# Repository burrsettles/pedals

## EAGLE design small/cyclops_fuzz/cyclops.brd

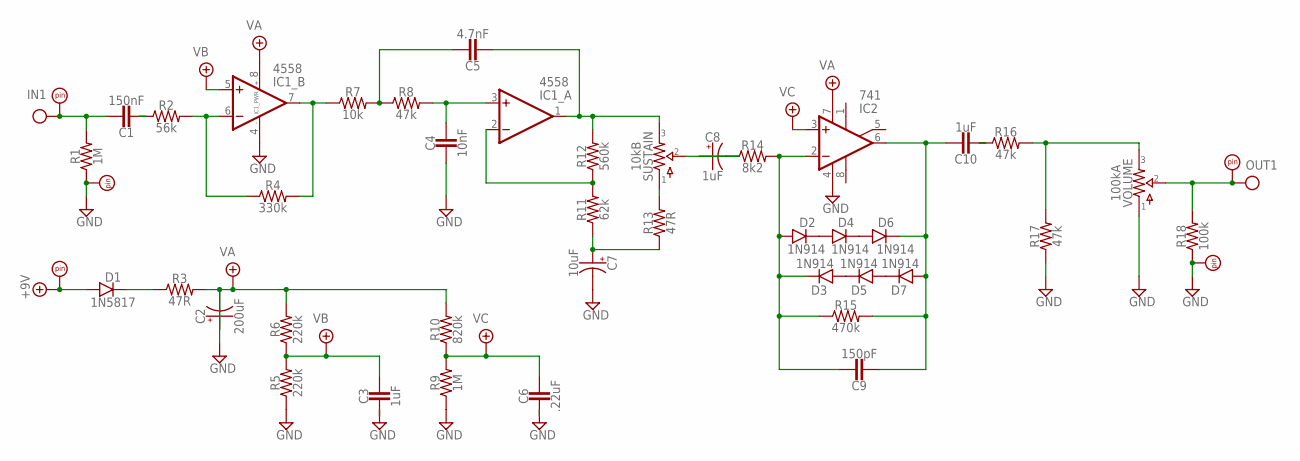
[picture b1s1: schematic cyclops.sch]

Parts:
C1: 150nF; BOX_SMALL
C2: 200uF; 063_025
C3, C10: 1uF; BOX_MED
C4: 10nF; BOX_SMALL
C5: 4.7nF; BOX_SMALL
C6: .22uF; BOX_SMALL
C7: 10uF; 050_020_1
C8: 1uF; 050_020_1
C9: 150pF; BOX_SMALL
D1: 1N5817; DO41-2
D2, D3, D4, D5, D6, D7: 1N914; DO35-2
IC1: 4558; DIL08
IC2: 741; DIL08
PAD1, PAD2, PAD5: PADSQR; SQUARE
PAD3, PAD4: PADRND; ROUND
R1, R9: 1M; R0207/2V
R2: 56k; R0207/2V
R3, R13: 47R; R0207/2V
R4: 330k; R0207/2V
R5, R6: 220k; R0207/2V
R7: 10k; R0207/2V
R8, R16, R17: 47k; R0207/2V
R10: 820k; R0207/2V
R11: 62k; R0207/2V
R12: 560k; R0207/2V
R14: 8k2; R0207/2V
R15: 470k; R0207/2V
R18: 100k; R0207/2V
SUSTAIN: 10kB; 2262_TRIM
VOLUME: 100kA; PADS_SMALL

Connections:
+9V: D1.A, PAD1.1
GND: C2.-, C3.2, C4.2, C6.2, C7.-, IC1.4 (V-), IC2.4 (V-), PAD3.1, PAD4.1, R1.1, R5.1, R9.1, R17.1, R18.1, VOLUME.1
IN: C1.1, PAD2.1, R1.2
unnamed: C1.2, R2.1
unnamed: C10.2, R16.1
unnamed: R16.2, R17.2, VOLUME.3
unnamed: IC1.6 (-IN), R2.2, R4.1
unnamed: IC1.7 (OUT), R4.2, R7.1
unnamed: C5.1, R7.2, R8.1
unnamed: C4.1, IC1.3 (+IN), R8.2
unnamed: C5.2, IC1.1 (OUT), R12.2, SUSTAIN.3
unnamed: IC1.2 (-IN), R11.2, R12.1
unnamed: C7.+, R11.1, R13.1
unnamed: R13.2, SUSTAIN.1
unnamed: D1.C, R3.1
unnamed: C8.-, SUSTAIN.2
unnamed: C8.+, R14.1
unnamed: C9.1, D2.A, D3.C, IC2.2 (-IN), R14.2, R15.1
unnamed: D2.C, D4.A
unnamed: D4.C, D6.A
unnamed: D5.A, D7.C
unnamed: D3.A, D5.C
unnamed: C9.2, C10.1, D6.C, D7.A, IC2.6 (OUT), R15.2
OUT: PAD5.1, R18.2, VOLUME.2
VA: C2.+, IC1.8 (V+), IC2.7 (V+), R3.2, R6.2, R10.2
VB: C3.1, IC1.5 (+IN), R5.2, R6.1
VC: C6.1, IC2.3 (+IN), R9.2, R10.1

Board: 2 copper layers, 44 parts (0 on the bottom side), 27 nets, no tracks yet.

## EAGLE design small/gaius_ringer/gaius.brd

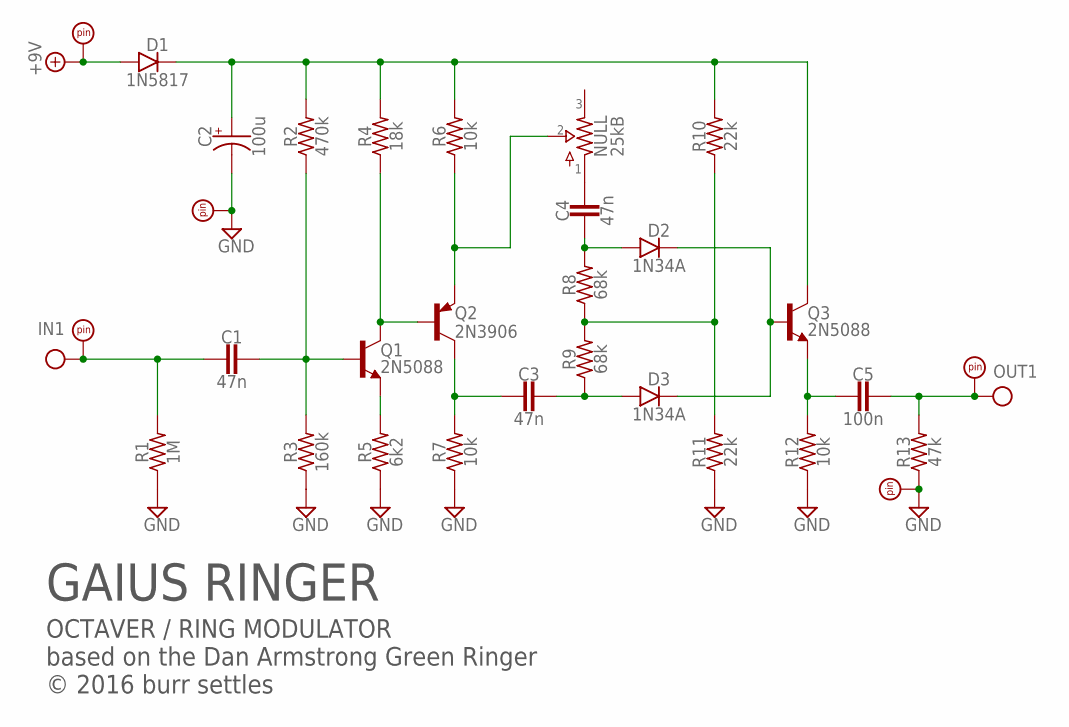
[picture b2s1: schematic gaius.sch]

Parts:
C1, C3, C4: 47n; BOX_SMALL
C2: 100u; 050_020_1
C5: 100n; BOX_SMALL
D1: 1N5817; DO41-2
D2, D3: 1N34A; DO35-2
NULL: 25kB; 2262_TRIM
PAD1, PAD2, PAD5: PADSQR; SQUARE
PAD3, PAD4: PADRND; ROUND
Q1, Q3: 2N5088; TO92-
Q2: 2N3906; TO92-
R1: 1M; R0207/3
R2: 470k; R0207/3
R3: 160k; R0207/3
R4: 18k; R0207/3
R5: 6k2; R0207/3
R6, R7, R12: 10k; R0207/3
R8, R9: 68k; R0207/3
R10, R11: 22k; R0207/3
R13: 47k; R0207/3

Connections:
+9V: D1.A, PAD1.1
GND: C2.-, PAD3.1, PAD4.1, R1.1, R3.1, R5.1, R7.1, R11.1, R12.1, R13.1
IN1: C1.2, PAD2.1, R1.2
unnamed: Q1.1 (C), Q2.2 (B), R4.1
unnamed: Q1.3 (E), R5.2
unnamed: C1.1, Q1.2 (B), R2.1, R3.2
unnamed: C4.2, D2.A, R8.2
unnamed: NULL.2, Q2.3 (E), R6.1
unnamed: R8.1, R9.2, R10.1, R11.2
unnamed: C4.1, NULL.1
unnamed: C3.2, Q2.1 (C), R7.2
unnamed: C3.1, D3.A, R9.1
unnamed: C5.2, Q3.3 (E), R12.2
unnamed: D2.C, D3.C, Q3.2 (B)
unnamed: C2.+, D1.C, Q3.1 (C), R2.2, R4.2, R6.2, R10.2
OUT1: C5.1, PAD5.1, R13.2

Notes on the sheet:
GAIUS RINGER
OCTAVER / RING MODULATOR based on the Dan Armstrong Green Ringer © 2016 burr settles

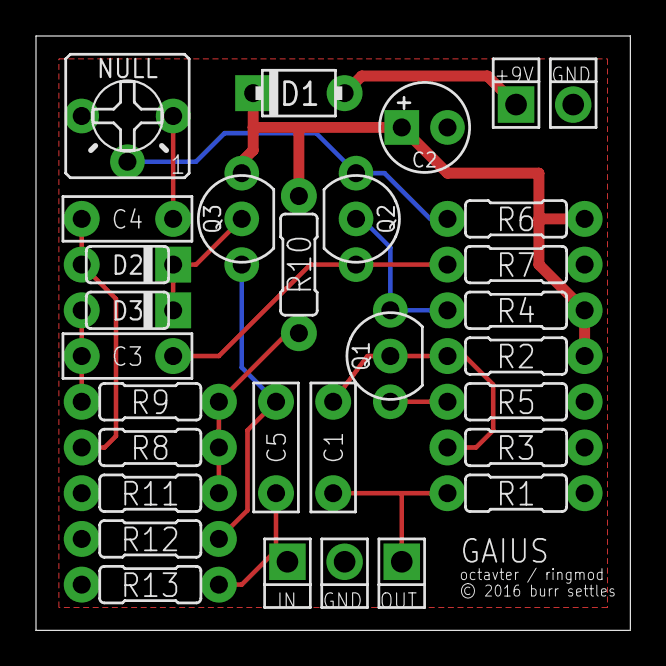
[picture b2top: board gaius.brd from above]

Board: 2 copper layers, 33.0 x 33.0 mm, 30 parts (0 on the bottom side), 16 nets.

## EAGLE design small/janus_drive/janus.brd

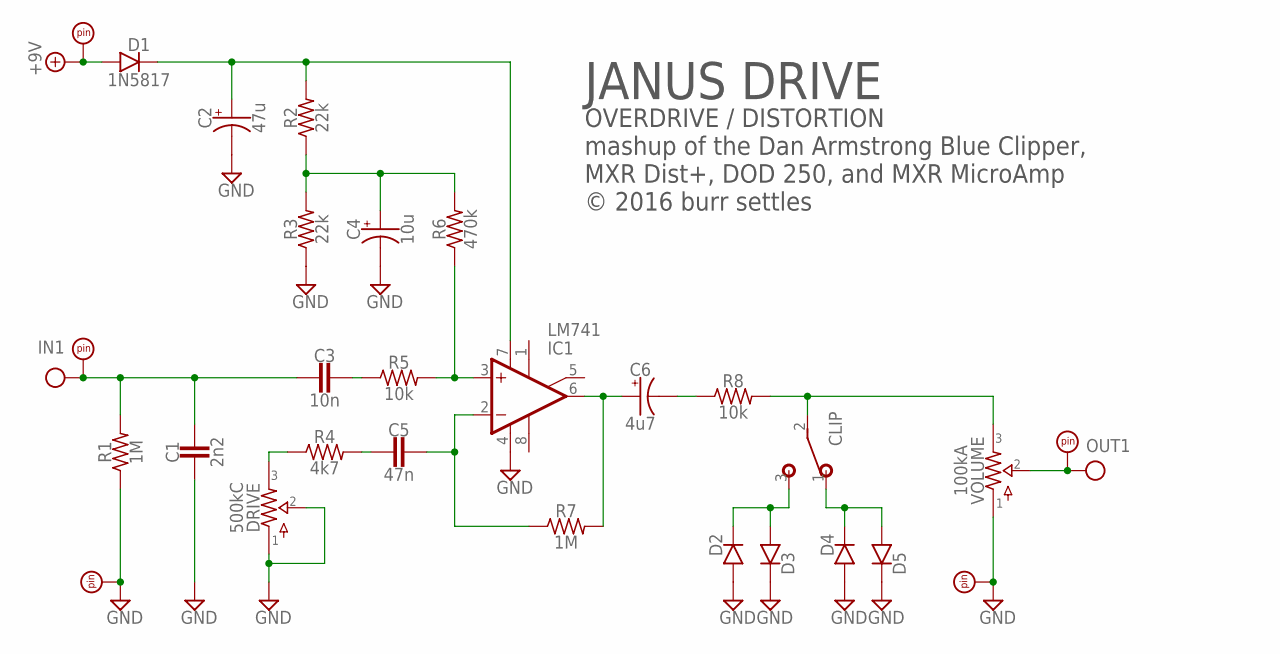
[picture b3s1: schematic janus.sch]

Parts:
C1: 2n2; BOX_SMALL
C2: 47u; 050_020_1
C3: 10n; BOX_SMALL
C4: 10u; 050_020_1
C5: 47n; BOX_SMALL
C6: 4u7; 050_020_1
CLIP: SPDTPADS; SPDT
D1: 1N5817; DO41-2
D2, D3: DO35.2; DO35-2
D4, D5: DO35.3; DO35-3
DRIVE: 500kC; PADS_SMALL
IC1: LM741; DIL08
PAD1, PAD2, PAD5: PADSQR; SQUARE
PAD3, PAD4: PADRND; ROUND
R1, R7: 1M; R0207/3
R2, R3: 22k; R0207/3
R4: 4k7; R0207/3
R5, R8: 10k; R0207/3
R6: 470k; R0207/3
VOLUME: 100kA; PADS_SMALL

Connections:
+9V: D1.A, PAD1.1
CLIP: CLIP.2, R8.2, VOLUME.3
GND: C1.1, C2.-, C4.-, D2.A, D3.C, D4.A, D5.C, DRIVE.1, DRIVE.2, IC1.4 (V-), PAD3.1, PAD4.1, R1.1, R3.1, VOLUME.1
IN: C1.2, C3.2, PAD2.1, R1.2
unnamed: C3.1, R5.1
unnamed: IC1.3 (+IN), R5.2, R6.1
unnamed: C5.1, IC1.2 (-IN), R7.1
unnamed: C5.2, R4.2
unnamed: C6.+, IC1.6 (OUT), R7.2
unnamed: C6.-, R8.1
unnamed: CLIP.3 (S), D2.C, D3.A
unnamed: C4.+, R2.1, R3.2, R6.2
unnamed: CLIP.1 (O), D4.C, D5.A
unnamed: DRIVE.3, R4.1
unnamed: C2.+, D1.C, IC1.7 (V+), R2.2
OUT: PAD5.1, VOLUME.2

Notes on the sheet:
JANUS DRIVE
OVERDRIVE / DISTORTION mashup of the Dan Armstrong Blue Clipper, MXR Dist+, DOD 250, and MXR MicroAmp © 2016 burr settles

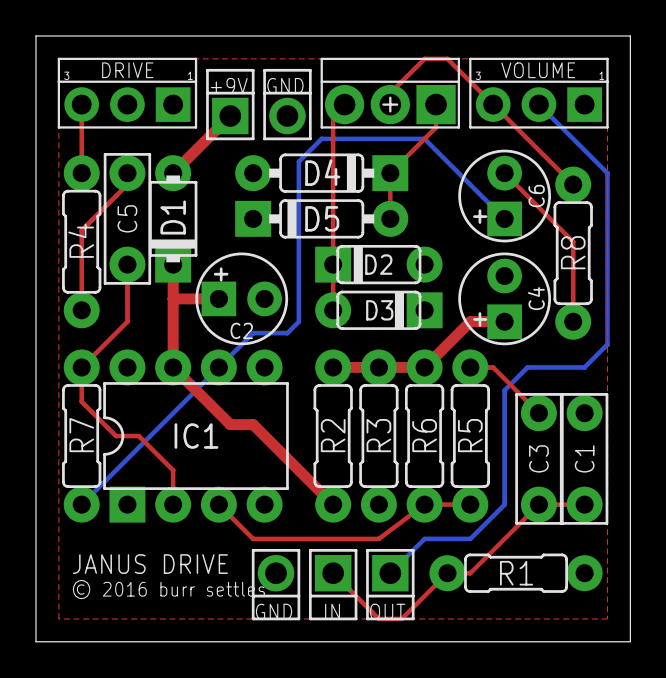
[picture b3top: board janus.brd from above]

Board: 2 copper layers, 33.0 x 33.7 mm, 28 parts (1 on the bottom side), 16 nets.

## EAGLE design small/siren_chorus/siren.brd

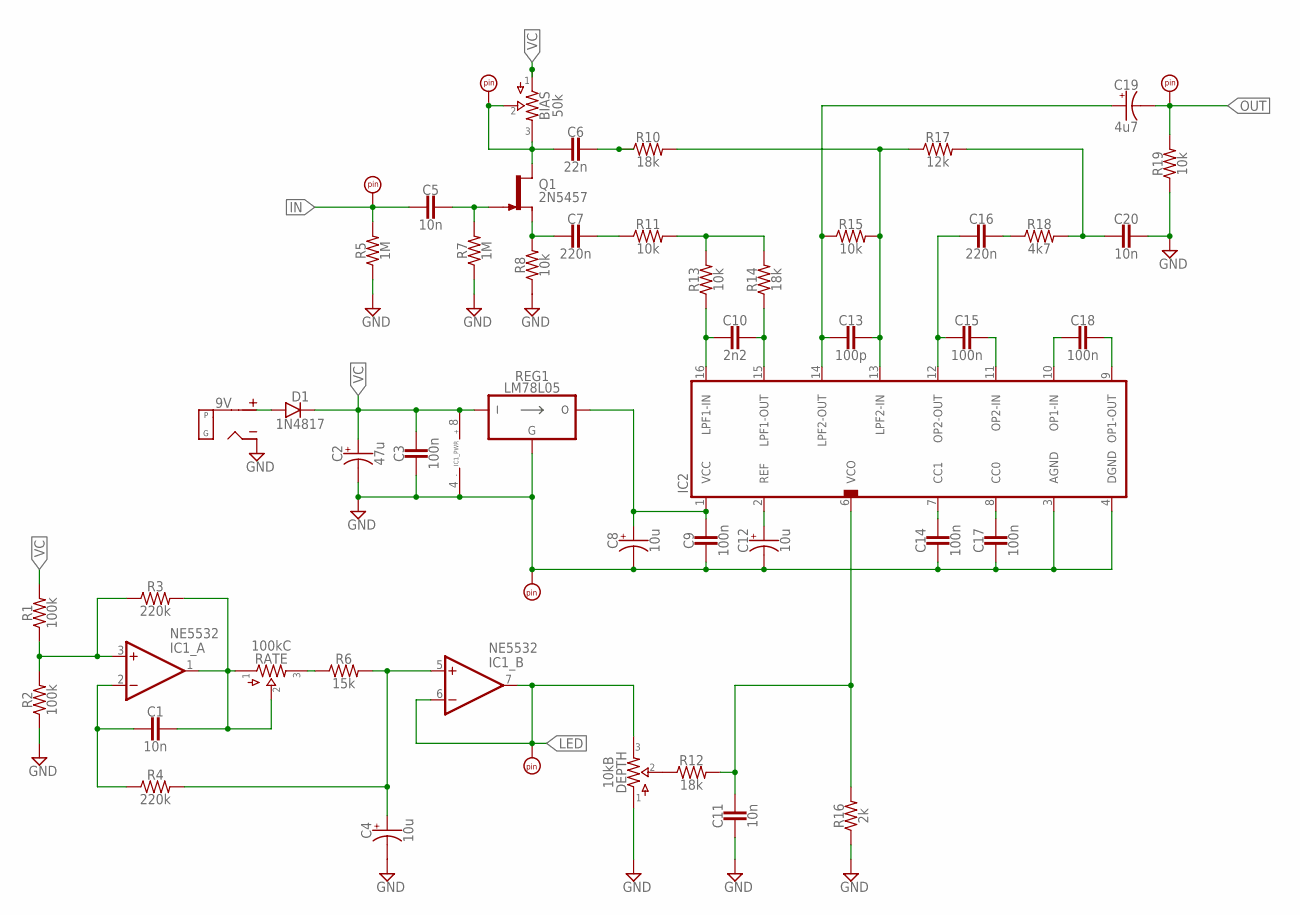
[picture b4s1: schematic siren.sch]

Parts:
9V: DC_MONO; DC
BIAS: 50k; 2262_TRIM
C1, C5, C11, C20: 10n; 050X030_025_2
C2: 47u; 050_020_1
C3, C9, C14, C15, C17, C18: 100n; 050X030_025_2
C4, C12: 10u; 050_020_1
C6: 22n; 050X030_025_2
C7, C16: 220n; 050X030_025_2
C8: 10u; 050_020
C10: 2n2; 050X030_025_2
C13: 100p; 050X030_025_2
C19: 4u7; 050_020_1
D1: 1N4817; DO41-3
DEPTH: 10kB; PADS_SMALL
GND: PADRND; ROUND
IC1: NE5532; DIL08
IC2: PT2399TH; DIL16
IN: PADSQR; SQUARE
LED: PADSQR; SQUARE
OUT: PADSQR; SQUARE
PAD2: PAD; UNLABELED
Q1: 2N5457; TO92-
R1, R2: 100k; R0207/2V
R3, R4: 220k; R0207/2V
R5, R7: 1M; R0207/2V
R6: 15k; R0207/2V
R8, R11, R13, R15, R19: 10k; R0207/2V
R10, R12, R14: 18k; R0207/2V
R16: 2k; R0207/2V
R17: 12k; R0207/2V
R18: 4k7; R0207/2V
RATE: 100kC; PADS_SMALL
REG1: LM78L05; TO92-

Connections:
+9V: 9V.T (TIP), D1.A
GND: 9V.S (SLEEVE), C2.-, C3.2, C4.-, C8.-, C9.2, C11.2, C12.-, C14.2, C17.2, C20.1, DEPTH.1, GND.1, IC1.4 (V-), IC2.3 (AGND), IC2.4 (DGND), R2.1, R5.1, R7.1, R8.1, R16.1, R19.1, REG1.2 (GND)
IN: C5.2, IN.1, R5.2
LED: DEPTH.3, IC1.6 (-IN), IC1.7 (OUT), LED.1
unnamed: C8.+, C9.1, IC2.1 (VCC), REG1.3 (VO)
unnamed: C10.2, IC2.16 (LPF1-IN), R13.1
unnamed: C10.1, IC2.15 (LPF1-OUT), R14.1
unnamed: C20.2, R17.2, R18.2
unnamed: C12.+, IC2.2 (REF)
unnamed: C14.1, IC2.7 (CC1)
unnamed: C17.1, IC2.8 (CC0)
unnamed: C15.1, IC2.11 (OP2-IN)
unnamed: C18.2, IC2.10 (OP1-IN)
unnamed: C18.1, IC2.9 (OP1-OUT)
unnamed: C13.2, C19.+, IC2.14 (LPF2-OUT), R15.1
unnamed: C13.1, IC2.13 (LPF2-IN), R10.2, R15.2, R17.1
unnamed: R11.2, R13.2, R14.2
unnamed: C7.1, R11.1
unnamed: C7.2, Q1.2 (S), R8.2
unnamed: C6.1, R10.1
unnamed: BIAS.2, BIAS.3, C6.2, PAD2.P$1, Q1.3 (D)
unnamed: C5.1, Q1.1 (G), R7.2
unnamed: IC1.3 (+IN), R1.1, R2.2, R3.1
unnamed: C15.2, C16.2, IC2.12 (OP2-OUT)
unnamed: C16.1, R18.1
unnamed: C1.1, IC1.1 (OUT), R3.2, RATE.1, RATE.2
unnamed: C1.2, IC1.2 (-IN), R4.1
unnamed: DEPTH.2, R12.1
unnamed: R6.1, RATE.3
unnamed: C4.+, IC1.5 (+IN), R4.2, R6.2
unnamed: C11.1, IC2.6 (VCO), R12.2, R16.2
OUT: C19.-, OUT.1, R19.2
VC: BIAS.1, C2.+, C3.1, D1.C, IC1.8 (V+), R1.2, REG1.1 (VI)

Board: 2 copper layers, 52 parts (1 on the bottom side), 33 nets, no tracks yet.

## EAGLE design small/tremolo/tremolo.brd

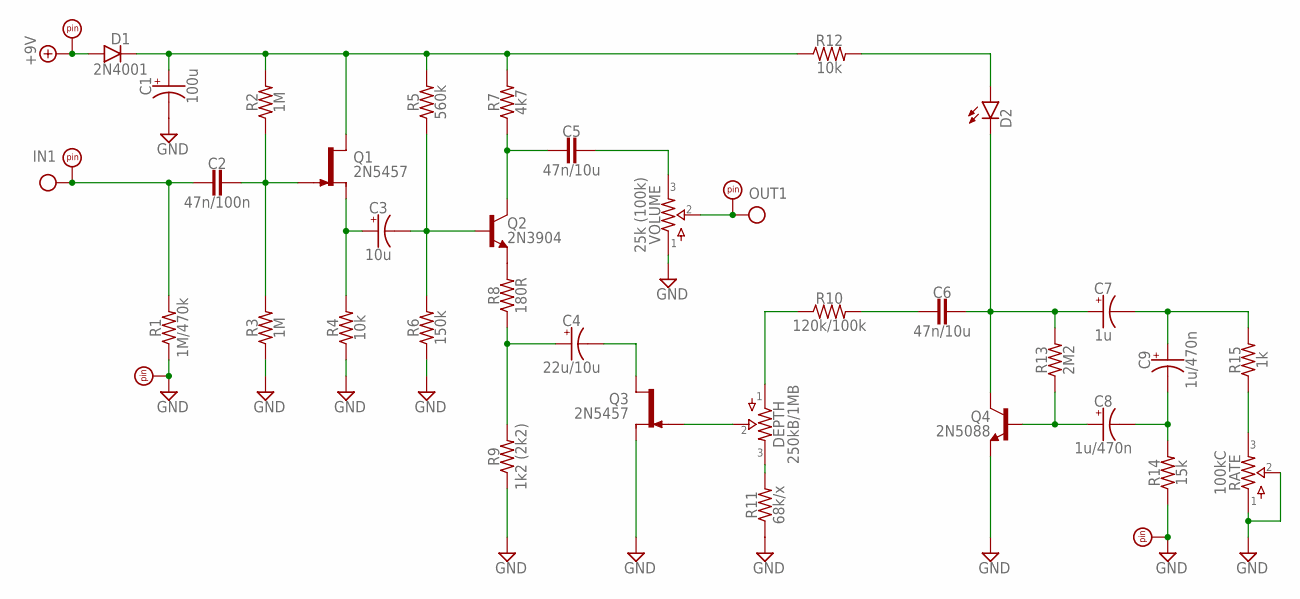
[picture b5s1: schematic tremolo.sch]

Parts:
C1: 100u; 050_020_1
C2: 47n/100n; BOX_SMALL
C3: 10u; 050_020_1
C4: 22u/10u; 050_020_1
C5, C6: 47n/10u; BOX_SMALL
C7: 1u; 050_020_1
C8, C9: 1u/470n; 050_020_1
D1: 2N4001; DO41-2
D2: LEDA; 3MM_A
DEPTH: 250kB/1MB; PADS_SMALL
PAD1, PAD2, PAD3: PADSQR; SQUARE
PAD4, PAD5: PADRND; ROUND
Q1, Q3: 2N5457; TO92-
Q2: 2N3904; TO92-
Q4: 2N5088; TO92-
R1: 1M/470k; R0207/3
R2, R3: 1M; R0207/3
R4, R12: 10k; R0207/3
R5: 560k; R0207/3
R6: 150k; R0207/3
R7: 4k7; R0207/3
R8: 180R; R0207/3
R9: 1k2 (2k2); R0207/3
R10: 120k/100k; R0207/3
R11: 68k/x; R0207/3
R13: 2M2; R0207/3
R14: 15k; R0207/3
R15: 1k; R0207/3
RATE: 100kC; PADS_SMALL
VOLUME: 25k (100k); 2262_TRIM

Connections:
+9V: D1.A, PAD1.1
GND: C1.-, PAD4.1, PAD5.1, Q3.2 (S), Q4.3 (E), R1.1, R3.1, R4.1, R6.1, R9.1, R11.1, R14.1, RATE.1, RATE.2, VOLUME.1
IN: C2.2, PAD2.1, R1.2
unnamed: C2.1, Q1.1 (G), R2.1, R3.2
unnamed: C3.+, Q1.2 (S), R4.2
unnamed: C3.-, Q2.2 (B), R5.1, R6.2
unnamed: C5.2, Q2.1 (C), R7.1
unnamed: Q2.3 (E), R8.2
unnamed: C5.1, VOLUME.3
unnamed: C1.+, D1.C, Q1.3 (D), R2.2, R5.2, R7.2, R12.1
unnamed: C4.+, R8.1, R9.2
unnamed: C4.-, Q3.3 (D)
unnamed: DEPTH.2, Q3.1 (G)
unnamed: DEPTH.1, R10.1
unnamed: C6.2, R10.2
unnamed: C6.1, C7.+, D2.K (C), Q4.1 (C), R13.2
unnamed: C8.+, Q4.2 (B), R13.1
unnamed: C7.-, C9.+, R15.2
unnamed: C8.-, C9.-, R14.2
unnamed: DEPTH.3, R11.2
unnamed: R15.1, RATE.3
unnamed: D2.A, R12.2
OUT: PAD3.1, VOLUME.2

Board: 2 copper layers, 38 parts (0 on the bottom side), 23 nets, no tracks yet.

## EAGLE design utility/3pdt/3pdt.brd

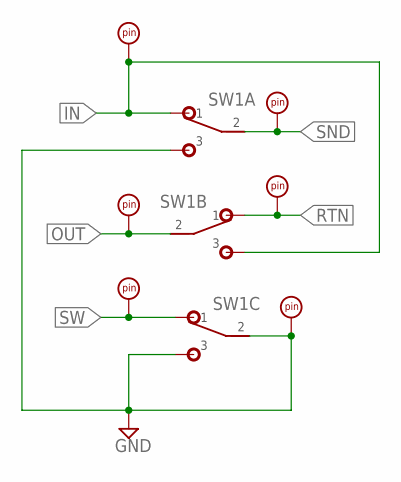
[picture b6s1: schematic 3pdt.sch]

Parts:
GND: PADRND; ROUND
IN: PADSQR; SQUARE
OUT: PADSQR; SQUARE
RTN: PADSQR; SQUARE
SND: PADSQR; SQUARE
SW: PADRND; ROUND
SW1: 3PDT

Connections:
GND: GND.1, SW1.A3 (3), SW1.C2 (2), SW1.C3 (3)
IN: IN.1, SW1.A1 (1), SW1.B3 (3)
OUT: OUT.1, SW1.B2 (2)
RTN: RTN.1, SW1.B1 (1)
SND: SND.1, SW1.A2 (2)
SW: SW.1, SW1.C1 (1)

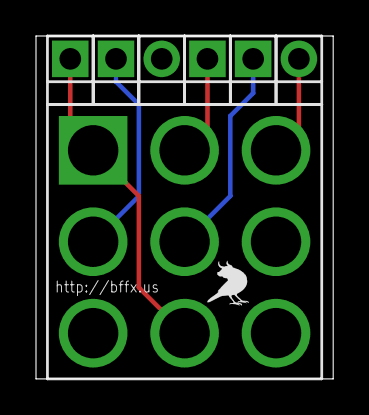
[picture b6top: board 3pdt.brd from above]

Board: 2 copper layers, 16.5 x 19.1 mm, 8 parts (0 on the bottom side), 6 nets.

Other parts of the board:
U$1: BF0100

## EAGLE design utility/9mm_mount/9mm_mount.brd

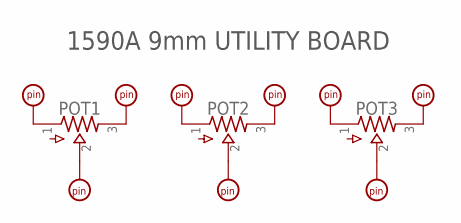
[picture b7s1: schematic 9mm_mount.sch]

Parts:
PAD1, PAD2, PAD3, PAD4, PAD5, PAD6, PAD7, PAD8, PAD9: PAD; UNLABELED
POT1, POT2, POT3: POTS9MM_VERT_ALT; 9MM_VERT_ALT

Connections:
unnamed: PAD1.P$1, POT1.1
unnamed: PAD2.P$1, POT1.3
unnamed: PAD3.P$1, POT2.1
unnamed: PAD4.P$1, POT2.3
unnamed: PAD5.P$1, POT3.1
unnamed: PAD6.P$1, POT3.3
unnamed: PAD7.P$1, POT1.2
unnamed: PAD8.P$1, POT2.2
unnamed: PAD9.P$1, POT3.2

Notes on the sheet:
1590A 9mm UTILITY BOARD

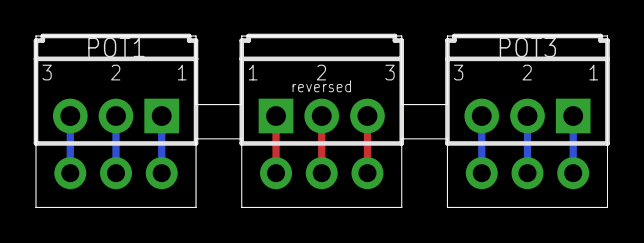
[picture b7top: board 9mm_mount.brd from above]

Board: 2 copper layers, 31.8 x 9.5 mm, 12 parts (1 on the bottom side), 9 nets.

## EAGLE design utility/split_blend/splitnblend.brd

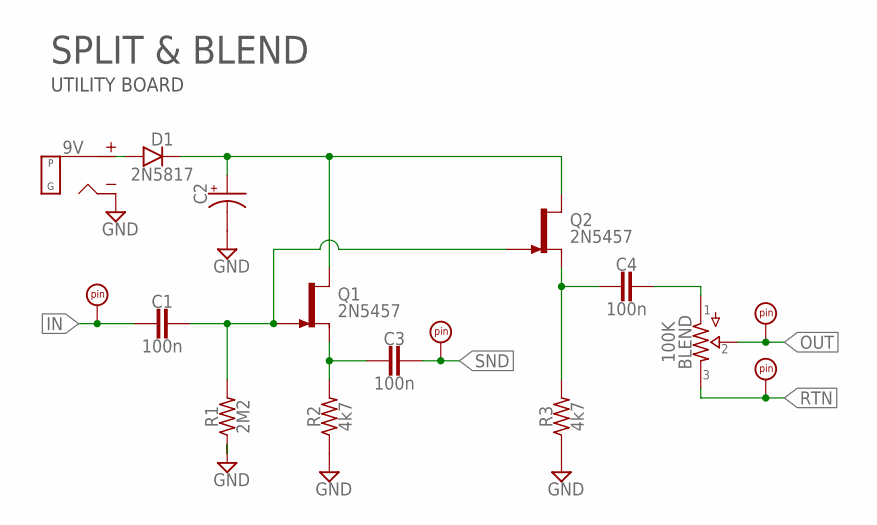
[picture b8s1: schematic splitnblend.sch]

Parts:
9V: DC_MONO; DC
BLEND: 100K; 16MM
C1, C3, C4: 100n; 050X030_025_2
C2: 0501; 050_020_1
D1: 2N5817; DO41-3
IN: PADSQR; SQUARE
OUT: PADSQR; SQUARE
Q1, Q2: 2N5457; TO92-
R1: 2M2; R0207/3
R2, R3: 4k7; R0207/3
RTN: PADSQR; SQUARE
SND: PADSQR; SQUARE

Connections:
GND: 9V.S (SLEEVE), C2.-, R1.1, R2.1, R3.1
IN: C1.2, IN.1
unnamed: 9V.T (TIP), D1.A
unnamed: C2.+, D1.C, Q1.3 (D), Q2.3 (D)
unnamed: C3.2, Q1.2 (S), R2.2
unnamed: C1.1, Q1.1 (G), Q2.1 (G), R1.2
unnamed: C4.2, Q2.2 (S), R3.2
unnamed: BLEND.1, C4.1
OUT: BLEND.2, OUT.1
RTN: BLEND.3, RTN.1
SND: C3.1, SND.1

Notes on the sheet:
SPLIT & BLEND
UTILITY BOARD

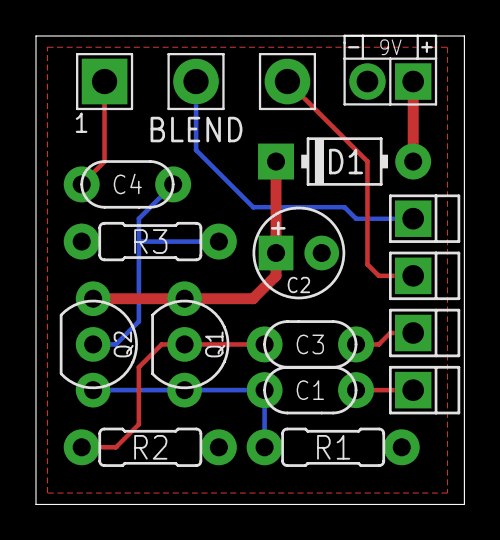
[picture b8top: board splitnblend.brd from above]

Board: 2 copper layers, 23.8 x 26.0 mm, 16 parts (0 on the bottom side), 11 nets.
